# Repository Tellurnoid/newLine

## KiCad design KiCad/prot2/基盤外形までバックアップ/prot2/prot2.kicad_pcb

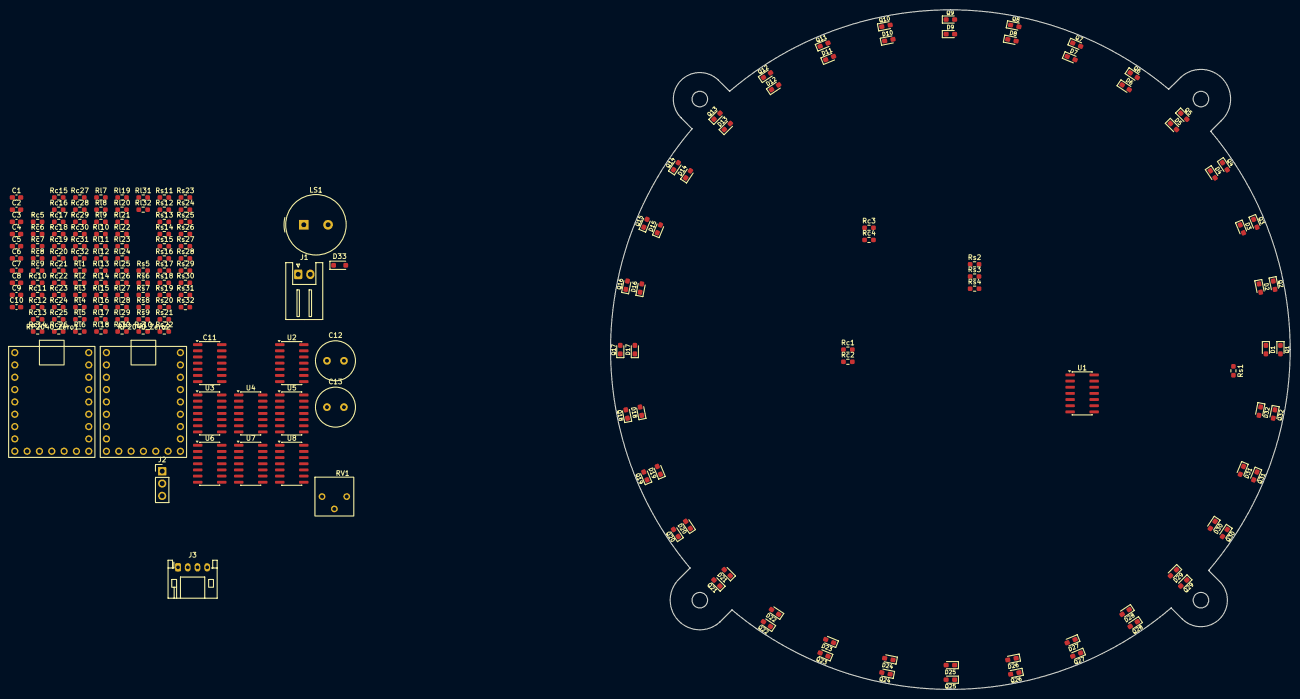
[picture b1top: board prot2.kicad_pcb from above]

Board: 2 copper layers, 140.0 x 140.0 mm, 193 parts (0 on the bottom side), 74 nets, no tracks yet.

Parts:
C1, C2, C3, C4, C5, C6, C7, C8, C9, C10: C; C_0603_1608Metric_Pad1.08x0.95mm_HandSolder
C11: C_Polarized_Small_US; SOIC-14_3.9x8.7mm_P1.27mm
C12, C13: C_Polarized_Small_US; C_Radial_D8.0mm_H11.5mm_P3.50mm
D1, D2, D3, D4, D5, D6, D7, D8, D9, D10, D11, D12, D13, D14, D15, D16, D17, D18, D19, D20, D21, D22, D23, D24, D25, D26, D27, D28, D29, D30, D31, D32: LED; LED_0603_1608Metric_Pad1.05x0.95mm_HandSolder
D33: D_Schottky; D_SOD-323_HandSoldering
H1, H2, H3, H4: MountingHole; MountingHole_3.2mm_M3
J1: Conn_01x02_Socket; JST_XH_S2B-XH-A_1x02_P2.50mm_Horizontal
J2: LED_SW; PinHeader_1x03_P2.54mm_Vertical
J3: Conn_01x04_Socket; JST_PH_S4B-PH-K_1x04_P2.00mm_Horizontal
LS1: Speaker_Crystal; Buzzer_TDK_PS1240P02BT_D12.2mm_H6.5mm
Q1, Q2, Q3, Q4, Q5, Q6, Q7, Q8, Q9, Q10, Q11, Q12, Q13, Q14, Q15, Q16, Q17, Q18, Q19, Q20, Q21, Q22, Q23, Q24, Q25, Q26, Q27, Q28, Q29, Q30, Q31, Q32: Q_Photo_NPN; LED_0603_1608Metric_Pad1.05x0.95mm_HandSolder
RP2040_Zero1, RP2040_Zero2: RP2040_zero
RV1: R_Potentiometer_Trim; hankotei_node
Rc1, Rc2, Rc3, Rc4, Rc5, Rc6, Rc7, Rc8, Rc9, Rc10, Rc11, Rc12, Rc13, Rc14, Rc15, Rc16, Rc17, Rc18, Rc19, Rc20, Rc21, Rc22, Rc23, Rc24, Rc25, Rc26, Rc27, Rc28, Rc29, Rc30, Rc31, Rc32: R; R_0603_1608Metric_Pad0.98x0.95mm_HandSolder
Rl1, Rl2, Rl3, Rl4, Rl5, Rl6, Rl7, Rl8, Rl9, Rl10, Rl11, Rl12, Rl13, Rl14, Rl15, Rl16, Rl17, Rl18, Rl19, Rl20, Rl21, Rl22, Rl23, Rl24, Rl25, Rl26, Rl27, Rl28, Rl29, Rl30, Rl31, Rl32: R; R_0603_1608Metric_Pad0.98x0.95mm_HandSolder
Rs1, Rs2, Rs3, Rs4, Rs5, Rs6, Rs7, Rs8, Rs9, Rs10, Rs11, Rs12, Rs13, Rs14, Rs15, Rs16, Rs17, Rs18, Rs19, Rs20, Rs21, Rs22, Rs23, Rs24, Rs25, Rs26, Rs27, Rs28, Rs29, Rs30, Rs31, Rs32: R; R_0603_1608Metric_Pad0.98x0.95mm_HandSolder
U1, U2, U3, U4, U5, U6, U7, U8: LM339; SOIC-14_3.9x8.7mm_P1.27mm

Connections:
1: Rc1.2, U1.2
2: Rc2.2, U1.1
3: Rc3.2, U1.13
4: Rc4.2, U1.14
5: Rc5.2, U2.2
6: Rc6.2, U2.1
7: Rc7.2, U2.13
8: Rc8.2, U2.14
9: Rc9.2, U3.2
10: Rc10.2, U3.1
11: Rc11.2, U3.13
12: Rc12.2, U3.14
13: Rc13.2, U4.2
14: Rc14.2, U4.1
15: Rc15.2, U4.13
16: Rc16.2, U4.14
17: Rc17.2, U5.2
18: Rc18.2, U5.1
19: Rc19.2, U5.13
20: Rc20.2, U5.14
21: Rc21.2, U6.2
22: Rc22.2, U6.1
23: Rc23.2, U6.13
24: Rc24.2, U6.14
25: Rc25.2, U7.2
26: Rc26.2, U7.1
27: Rc27.2, U7.13
28: Rc28.2, U7.14
29: Rc29.2, U8.2
30: Rc30.2, U8.1
31: Rc31.2, U8.13
32: Rc32.2, U8.14
GND: C1.2, C2.2, C3.2, C4.2, C5.2, C6.2, C7.2, C8.2, C9.2, C10.2, C11.2, C12.2, C13.2, J1.2, J3.4, RP2040_Zero1.22 (GND), RP2040_Zero2.22 (GND), RV1.3, Rl1.2, Rl2.2, Rl3.2, Rl4.2, Rl5.2, Rl6.2, Rl7.2, Rl8.2, Rl9.2, Rl10.2, Rl11.2, Rl12.2, Rl13.2, Rl14.2, Rl15.2, Rl16.2, Rl17.2, Rl18.2, Rl19.2, Rl20.2, Rl21.2, Rl22.2, Rl23.2, Rl24.2, Rl25.2, Rl26.2, Rl27.2, Rl28.2, Rl29.2, Rl30.2, Rl31.2, Rl32.2, Rs1.2, Rs2.2, Rs3.2, Rs4.2, Rs5.2, Rs6.2, Rs7.2, Rs8.2, Rs9.2, Rs10.2, Rs11.2, Rs12.2, Rs13.2, Rs14.2, Rs15.2, Rs16.2, Rs17.2, Rs18.2, Rs19.2, Rs20.2, Rs21.2, Rs22.2, Rs23.2, Rs24.2, Rs25.2, Rs26.2, Rs27.2, Rs28.2, Rs29.2, Rs30.2, Rs31.2, Rs32.2, U1.12 (V-), U2.12 (V-), U3.12 (V-), U4.12 (V-), U5.12 (V-), U6.12 (V-), U7.12 (V-), U8.12 (V-)
IMU_5V: C9.1, C10.1, C11.1, C12.1, D33.1 (K), RP2040_Zero1.23 (5V), RP2040_Zero2.23 (5V)
LED_5V: C13.1, D1.2 (A), D2.2 (A), D3.2 (A), D4.2 (A), D5.2 (A), D6.2 (A), D7.2 (A), D8.2 (A), D9.2 (A), D10.2 (A), D11.2 (A), D12.2 (A), D13.2 (A), D14.2 (A), D15.2 (A), D16.2 (A), D17.2 (A), D18.2 (A), D19.2 (A), D20.2 (A), D21.2 (A), D22.2 (A), D23.2 (A), D24.2 (A), D25.2 (A), D26.2 (A), D27.2 (A), D28.2 (A), D29.2 (A), D30.2 (A), D31.2 (A), D32.2 (A), J1.1, J2.3
unnamed: D1.1 (K), D2.1 (K), D3.1 (K), D4.1 (K), D5.1 (K), D6.1 (K), D7.1 (K), D8.1 (K), D9.1 (K), D10.1 (K), D11.1 (K), D12.1 (K), D13.1 (K), D14.1 (K), D15.1 (K), D16.1 (K), D17.1 (K), D18.1 (K), D19.1 (K), D20.1 (K), D21.1 (K), D22.1 (K), D23.1 (K), D24.1 (K), D25.1 (K), D26.1 (K), D27.1 (K), D28.1 (K), D29.1 (K), D30.1 (K), D31.1 (K), D32.1 (K), Rl1.1
unnamed: D33.2 (A), J3.3
unnamed: J2.1, J2.2
unnamed: Q1.2 (E), Q2.2 (E), Q3.2 (E), Q4.2 (E), Q5.2 (E), Q6.2 (E), Q7.2 (E), Q8.2 (E), Q9.2 (E), Q10.2 (E), Q11.2 (E), Q12.2 (E), Q13.2 (E), Q14.2 (E), Q15.2 (E), Q16.2 (E), Q17.2 (E), Q18.2 (E), Q19.2 (E), Q20.2 (E), Q21.2 (E), Q22.2 (E), Q23.2 (E), Q24.2 (E), Q25.2 (E), Q26.2 (E), Q27.2 (E), Q28.2 (E), Q29.2 (E), Q30.2 (E), Q31.2 (E), Q32.2 (E), Rs1.1, U1.4 (-)
unnamed: Rs2.1, U1.6 (-)
unnamed: Rs3.1, U1.10 (-)
unnamed: Rs4.1, U1.8 (-)
unnamed: Rs5.1, U2.4 (-)
unnamed: Rs6.1, U2.6 (-)
unnamed: Rs7.1, U2.10 (-)
unnamed: Rs8.1, U2.8 (-)
unnamed: Rs9.1, U3.4 (-)
unnamed: Rs10.1, U3.6 (-)
unnamed: Rs11.1, U3.10 (-)
unnamed: Rs12.1, U3.8 (-)
unnamed: Rs13.1, U4.4 (-)
unnamed: Rs14.1, U4.6 (-)
unnamed: Rs15.1, U4.10 (-)
unnamed: Rs16.1, U4.8 (-)
unnamed: Rs17.1, U5.4 (-)
unnamed: Rs18.1, U6.4 (-)
unnamed: Rs19.1, U7.4 (-)
unnamed: Rs20.1, U8.4 (-)
unnamed: Rs21.1, U5.6 (-)
unnamed: Rs22.1, U6.6 (-)
unnamed: Rs23.1, U7.6 (-)
unnamed: Rs24.1, U8.6 (-)
unnamed: Rs25.1, U5.10 (-)
unnamed: Rs26.1, U6.10 (-)
unnamed: Rs27.1, U7.10 (-)
unnamed: Rs28.1, U8.10 (-)
unnamed: Rs29.1, U5.8 (-)
unnamed: Rs30.1, U6.8 (-)
unnamed: Rs31.1, U7.8 (-)
unnamed: Rs32.1, U8.8 (-)
OUT_RX: J3.2, RP2040_Zero1.2 (1)
OUT_TX: J3.1, RP2040_Zero1.1 (0)
VCC: C1.1, C2.1, C3.1, C4.1, C5.1, C6.1, C7.1, C8.1, Q1.1 (C), Q2.1 (C), Q3.1 (C), Q4.1 (C), Q5.1 (C), Q6.1 (C), Q7.1 (C), Q8.1 (C), Q9.1 (C), Q10.1 (C), Q11.1 (C), Q12.1 (C), Q13.1 (C), Q14.1 (C), Q15.1 (C), Q16.1 (C), Q17.1 (C), Q18.1 (C), Q19.1 (C), Q20.1 (C), Q21.1 (C), Q22.1 (C), Q23.1 (C), Q24.1 (C), Q25.1 (C), Q26.1 (C), Q27.1 (C), Q28.1 (C), Q29.1 (C), Q30.1 (C), Q31.1 (C), Q32.1 (C), RP2040_Zero1.21 (3V3), RP2040_Zero2.21 (3V3), RV1.1, Rc1.1, Rc2.1, Rc3.1, Rc4.1, Rc5.1, Rc6.1, Rc7.1, Rc8.1, Rc9.1, Rc10.1, Rc11.1, Rc12.1, Rc13.1, Rc14.1, Rc15.1, Rc16.1, Rc17.1, Rc18.1, Rc19.1, Rc20.1, Rc21.1, Rc22.1, Rc23.1, Rc24.1, Rc25.1, Rc26.1, Rc27.1, Rc28.1, Rc29.1, Rc30.1, Rc31.1, Rc32.1, U1.3 (V+), U2.3 (V+), U3.3 (V+), U4.3 (V+), U5.3 (V+), U6.3 (V+), U7.3 (V+), U8.3 (V+)
conp_+: RV1.2, U1.5 (+), U1.7 (+), U1.9 (+), U1.11 (+), U2.5 (+), U2.7 (+), U2.9 (+), U2.11 (+), U3.5 (+), U3.7 (+), U3.9 (+), U3.11 (+), U4.5 (+), U4.7 (+), U4.9 (+), U4.11 (+), U5.5 (+), U5.7 (+), U5.9 (+), U5.11 (+), U6.5 (+), U6.7 (+), U6.9 (+), U6.11 (+), U7.5 (+), U7.7 (+), U7.9 (+), U7.11 (+), U8.5 (+), U8.7 (+), U8.9 (+), U8.11 (+)

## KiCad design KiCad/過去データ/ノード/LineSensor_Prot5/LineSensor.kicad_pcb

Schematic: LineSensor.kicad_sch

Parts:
A1: Arduino_Nano_v2.x; Arduino_Nano
C2: C; CP_Radial_D5.0mm_P2.50mm
C3: C; C_Disc_D7.5mm_W2.5mm_P5.00mm
C4, C5, C6, C7, C8, C9, C10, C11: C; C_0603_1608Metric
CN1, CN2: C_Network04
D34, D35, D36, D37, D38, D39, D40, D41, D42, D43, D44, D45, D46, D47, D48, D49: LED; LED_0603_1608Metric
H1, H2, H3, H4: MountingHole; MountingHole_3.2mm_M3
J1: Conn_01x04_Socket; JST_XH_B4B-XH-A_1x04_P2.50mm_Vertical
J2: Conn_01x02_Socket; JST_XH_B2B-XH-A_1x02_P2.50mm_Vertical
Q1, Q2, Q3, Q4, Q5, Q6, Q7, Q8, Q9, Q10, Q11, Q12, Q13, Q14, Q15, Q16: Q_Photo_NPN; NJL7502R
Q17: NMOS; TO-251-3-1EP_Horizontal_TabDown
R1, R2, R3, R4, R5, R6, R7, R8, R9, R10, R11, R12, R13, R14, R15, R16, R17, R18, R19, R20, R21, R22, R23, R24, R25, R26, R27, R28, R29, R30, R31, R32, R33, R34, R35, R36, R37, R38, R39, R40, R41, R42, R43, R44, R45, R46, R55, R56: R; R_0603_1608Metric_Pad0.98x0.95mm_HandSolder
R49, R50, R51, R84, R85: R; R_Axial_DIN0207_L6.3mm_D2.5mm_P7.62mm_Horizontal
RV1: R_Potentiometer_Trim; 名称未設定
SW2: SW_DPST_x2; PinSocket_1x03_P2.54mm_Vertical
U2, U3, U4, U5, U6, U7, U8, U9: LM393; SOIC-8_3.9x4.9mm_P1.27mm

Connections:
GND: A1.4 (GND), A1.29 (GND), C2.1, C3.2, C4.2, C5.2, C6.2, C7.2, C8.2, C9.2, C10.2, C11.2, J1.3, J2.2, Q17.3 (S), R1.2, R2.2, R3.2, R4.2, R9.2, R10.2, R11.2, R12.2, R13.2, R14.2, R15.2, R16.2, R17.2, R18.2, R19.2, R20.2, R50.2, R85.1, RV1.3, U2.4 (V-), U3.4 (V-), U4.4 (V-), U5.4 (V-), U6.4 (V-), U7.4 (V-), U8.4 (V-), U9.4 (V-)
unnamed: A1.2 (D0/RX), J1.2
unnamed: A1.1 (D1/TX), R49.2
unnamed: A1.13 (D10), R84.1
unnamed: D34.1 (K), R55.1
unnamed: D35.1 (K), R56.1
unnamed: D36.1 (K), R40.1
unnamed: D37.1 (K), R41.1
unnamed: D38.1 (K), R42.1
unnamed: D39.1 (K), R43.1
unnamed: D40.1 (K), R44.1
unnamed: D41.1 (K), R45.1
unnamed: D42.1 (K), R46.1
unnamed: D43.1 (K), R39.1
unnamed: D44.1 (K), R38.1
unnamed: D45.1 (K), R37.1
unnamed: D46.1 (K), R36.1
unnamed: D47.1 (K), R35.1
unnamed: D48.1 (K), R34.1
unnamed: D49.1 (K), R33.1
unnamed: J1.1, R49.1, R51.1
unnamed: J2.1, SW2.2 (B)
unnamed: Q1.2 (E), R4.1, U3.2 (-)
unnamed: Q2.2 (E), R3.1, U3.6 (-)
unnamed: Q3.2 (E), R2.1, U4.2 (-)
unnamed: Q4.2 (E), R1.1, U4.6 (-)
unnamed: Q5.2 (E), R13.1, U7.2 (-)
unnamed: Q6.2 (E), R14.1, U7.6 (-)
unnamed: Q7.2 (E), R16.1, U8.6 (-)
unnamed: Q8.2 (E), R15.1, U8.2 (-)
unnamed: Q9.2 (E), R9.1, U6.6 (-)
unnamed: Q10.2 (E), R10.1, U6.2 (-)
unnamed: Q11.2 (E), R11.1, U5.6 (-)
unnamed: Q12.2 (E), R12.1, U5.2 (-)
unnamed: Q13.2 (E), R17.1, U9.3 (+)
unnamed: Q14.2 (E), R18.1, U9.5 (+)
unnamed: Q15.2 (E), R19.1, U2.2 (-)
unnamed: Q16.2 (E), R20.1, U2.6 (-)
unnamed: Q17.1 (D), R33.2, R34.2, R35.2, R36.2, R37.2, R38.2, R39.2, R40.2, R41.2, R42.2, R43.2, R44.2, R45.2, R46.2, R55.2, R56.2
unnamed: Q17.2 (G), R84.2, R85.2
unnamed: R50.1, R51.2
unnamed: RV1.2, U2.3 (+), U2.5 (+), U3.3 (+), U3.5 (+), U4.3 (+), U4.5 (+), U5.3 (+), U5.5 (+), U6.3 (+), U6.5 (+), U7.3 (+), U7.5 (+), U8.3 (+), U8.5 (+), U9.2 (-), U9.6 (-)
U2A: A1.9 (D6), R31.2, U2.1
U2B: A1.10 (D7), R32.2, U2.7
U3A: A1.14 (D11), R5.2, U4.7
U3B: A1.15 (D12), R6.2, U4.1
U4A: A1.20 (A1), R7.2, U3.7
U4B: A1.19 (A0), R8.2, U3.1
U5A: A1.22 (A3), R24.2, U5.1
U5B: A1.21 (A2), R23.2, U5.7
U6A: A1.23 (A4), R22.2, U6.1
U6B: A1.24 (A5), R21.2, U6.7
U7A: A1.7 (D4), R28.2, U7.1
U7B: A1.8 (D5), R27.2, U7.7
U8A: A1.5 (D2), R26.2, U8.1
U8B: A1.6 (D3), R25.2, U8.7
U9A: A1.12 (D9), R29.2, U9.1
U9B: A1.11 (D8), R30.2, U9.7
VCC: A1.27 (+5V), C2.2, C3.1, C4.1, C5.1, C6.1, C7.1, C8.1, C9.1, C10.1, C11.1, D34.2 (A), D35.2 (A), D36.2 (A), D37.2 (A), D38.2 (A), D39.2 (A), D40.2 (A), D41.2 (A), D42.2 (A), D43.2 (A), D44.2 (A), D45.2 (A), D46.2 (A), D47.2 (A), D48.2 (A), D49.2 (A), J1.4, Q1.1 (C), Q2.1 (C), Q3.1 (C), Q4.1 (C), Q5.1 (C), Q6.1 (C), Q7.1 (C), Q8.1 (C), Q9.1 (C), Q10.1 (C), Q11.1 (C), Q12.1 (C), Q13.1 (C), Q14.1 (C), Q15.1 (C), Q16.1 (C), R5.1, R6.1, R7.1, R8.1, R21.1, R22.1, R23.1, R24.1, R25.1, R26.1, R27.1, R28.1, R29.1, R30.1, R31.1, R32.1, RV1.1, SW2.1 (A), U2.8 (V+), U3.8 (V+), U4.8 (V+), U5.8 (V+), U6.8 (V+), U7.8 (V+), U8.8 (V+), U9.8 (V+)

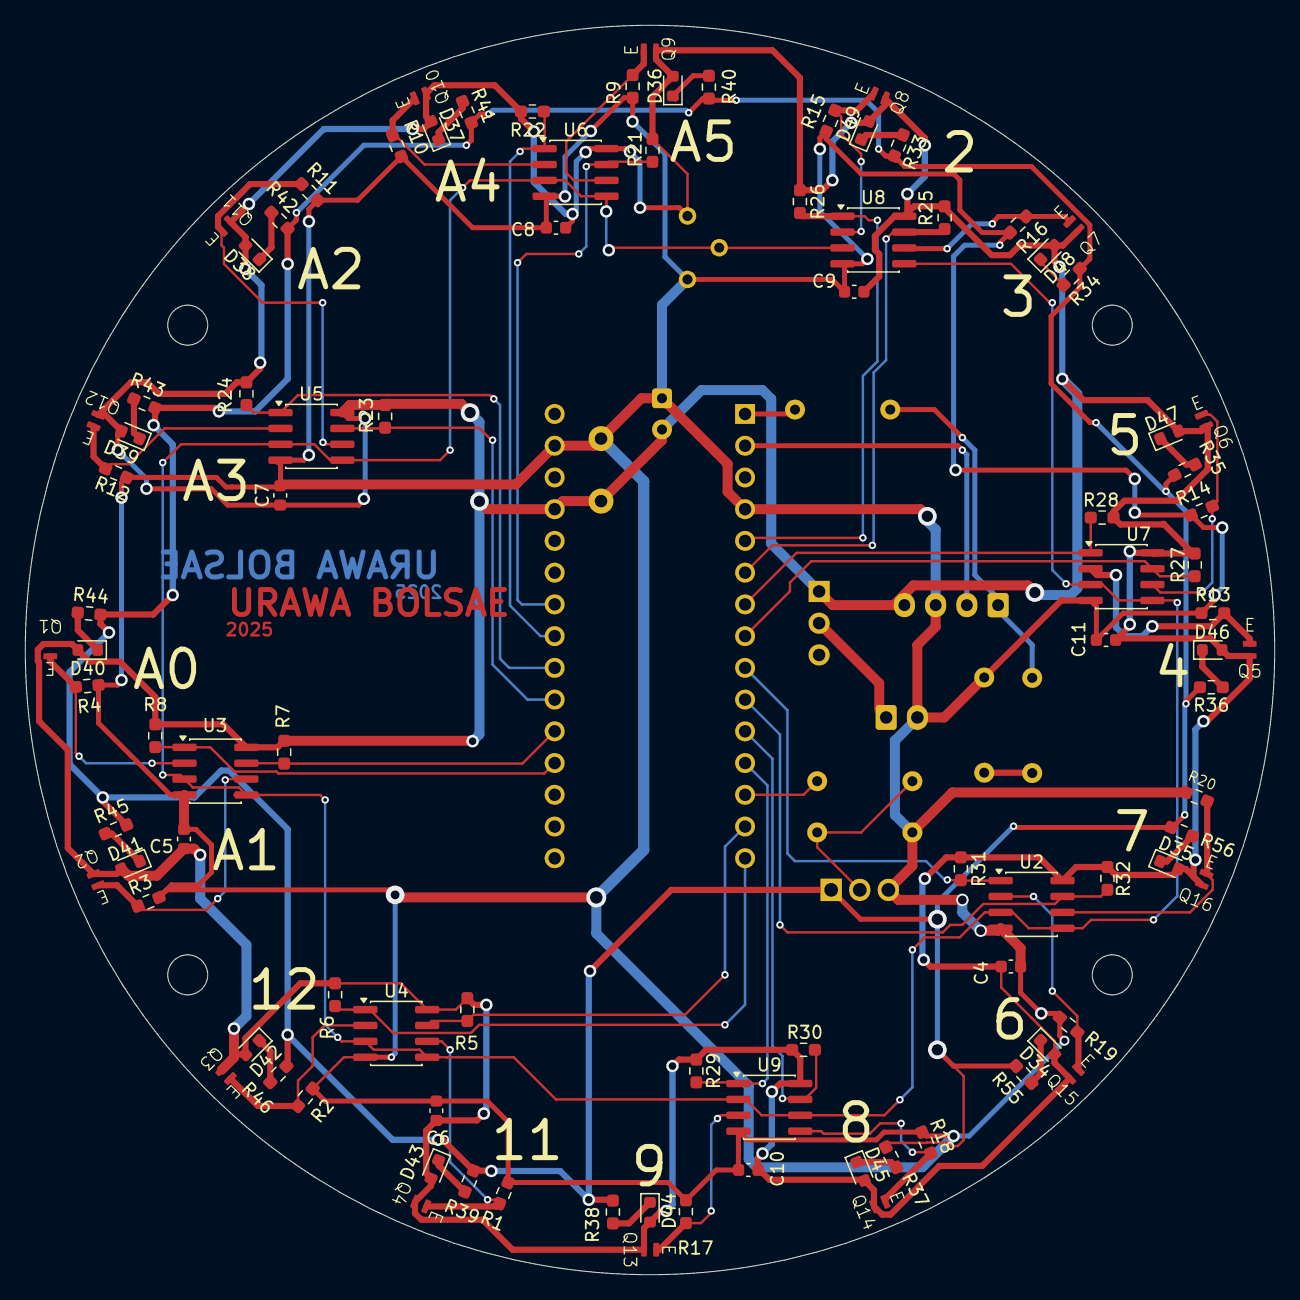
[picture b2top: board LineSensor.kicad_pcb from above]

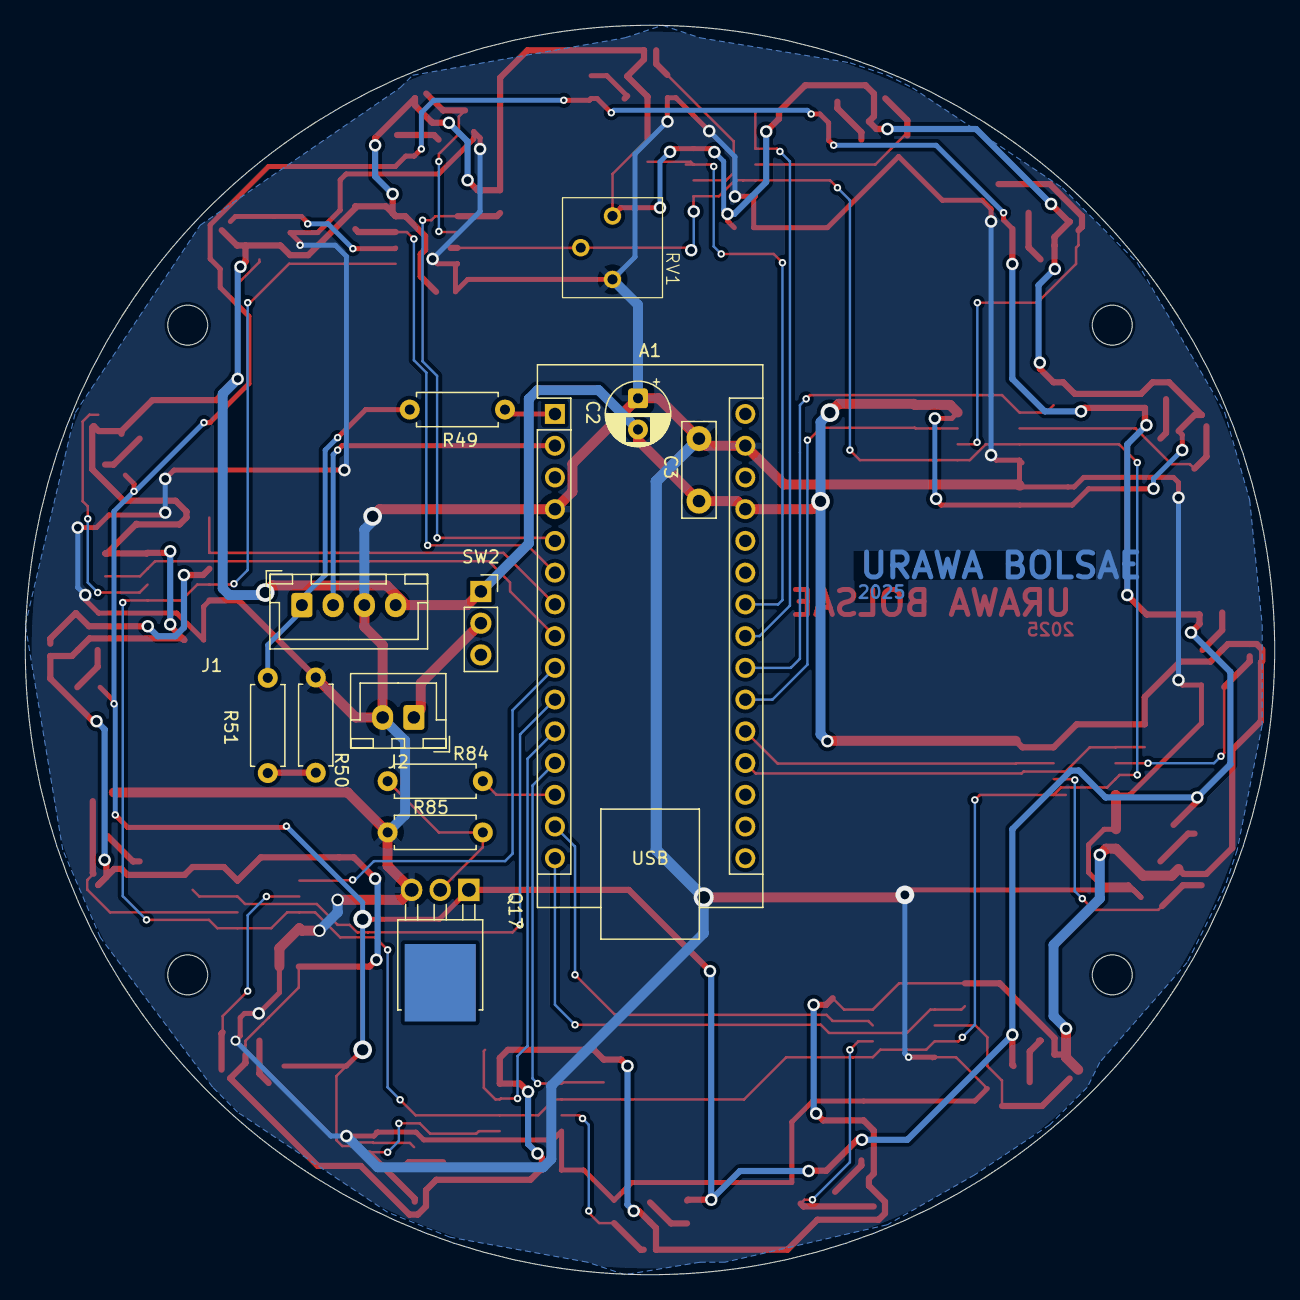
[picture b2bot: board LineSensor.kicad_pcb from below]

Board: 2 copper layers, 100.0 x 100.0 mm, 113 parts (13 on the bottom side), 59 nets.

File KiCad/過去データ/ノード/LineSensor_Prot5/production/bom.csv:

Designator,Footprint,Quantity,Value,LCSC Part #
A1,Arduino_Nano,1,Arduino_Nano_v2.x,
"C10, C11, C4, C5, C6, C7, C8, C9",0603,8,C,
C2,CP_Radial_D5.0mm_P2.50mm,1,C,
C3,C_Disc_D7.5mm_W2.5mm_P5.00mm,1,C,
"D34, D35, D36, D37, D38, D39, D40, D41, D42, D43, D44, D45, D46, D47, D48, D49",0603,16,LED,
J1,JST_XH_B4B-XH-A_1x04_P2.50mm_Vertical,1,Conn_01x04_Socket,
J2,JST_XH_B2B-XH-A_1x02_P2.50mm_Vertical,1,Conn_01x02_Socket,
"Q1, Q10, Q11, Q12, Q13, Q14, Q15, Q16, Q2, Q3, Q4, Q5, Q6, Q7, Q8, Q9",NJL7502R,16,Q_Photo_NPN,
Q17,TO-251-3-1EP_Horizontal_TabDown,1,NMOS,
"R1, R10, R11, R12, R13, R14, R15, R16, R17, R18, R19, R2, R20, R21, R22, R23, R24, R25, R26, R27, R28, R29, R3, R30, R31, R32, R33, R34, R35, R36, R37, R38, R39, R4, R40, R41, R42, R43, R44, R45, R46, R5, R55, R56, R6, R7, R8, R9",0603,48,R,
"R49, R50, R51, R84, R85",R_Axial_DIN0207_L6.3mm_D2.5mm_P7.62mm_Horizontal,5,R,
RV1,名称未設定,1,R_Potentiometer_Trim,
SW2,PinSocket_1x03_P2.54mm_Vertical,1,SW_DPST_x2,
"U2, U3, U4, U5, U6, U7, U8, U9",SOIC-8_3.9x4.9mm_P1.27mm,8,LM393,

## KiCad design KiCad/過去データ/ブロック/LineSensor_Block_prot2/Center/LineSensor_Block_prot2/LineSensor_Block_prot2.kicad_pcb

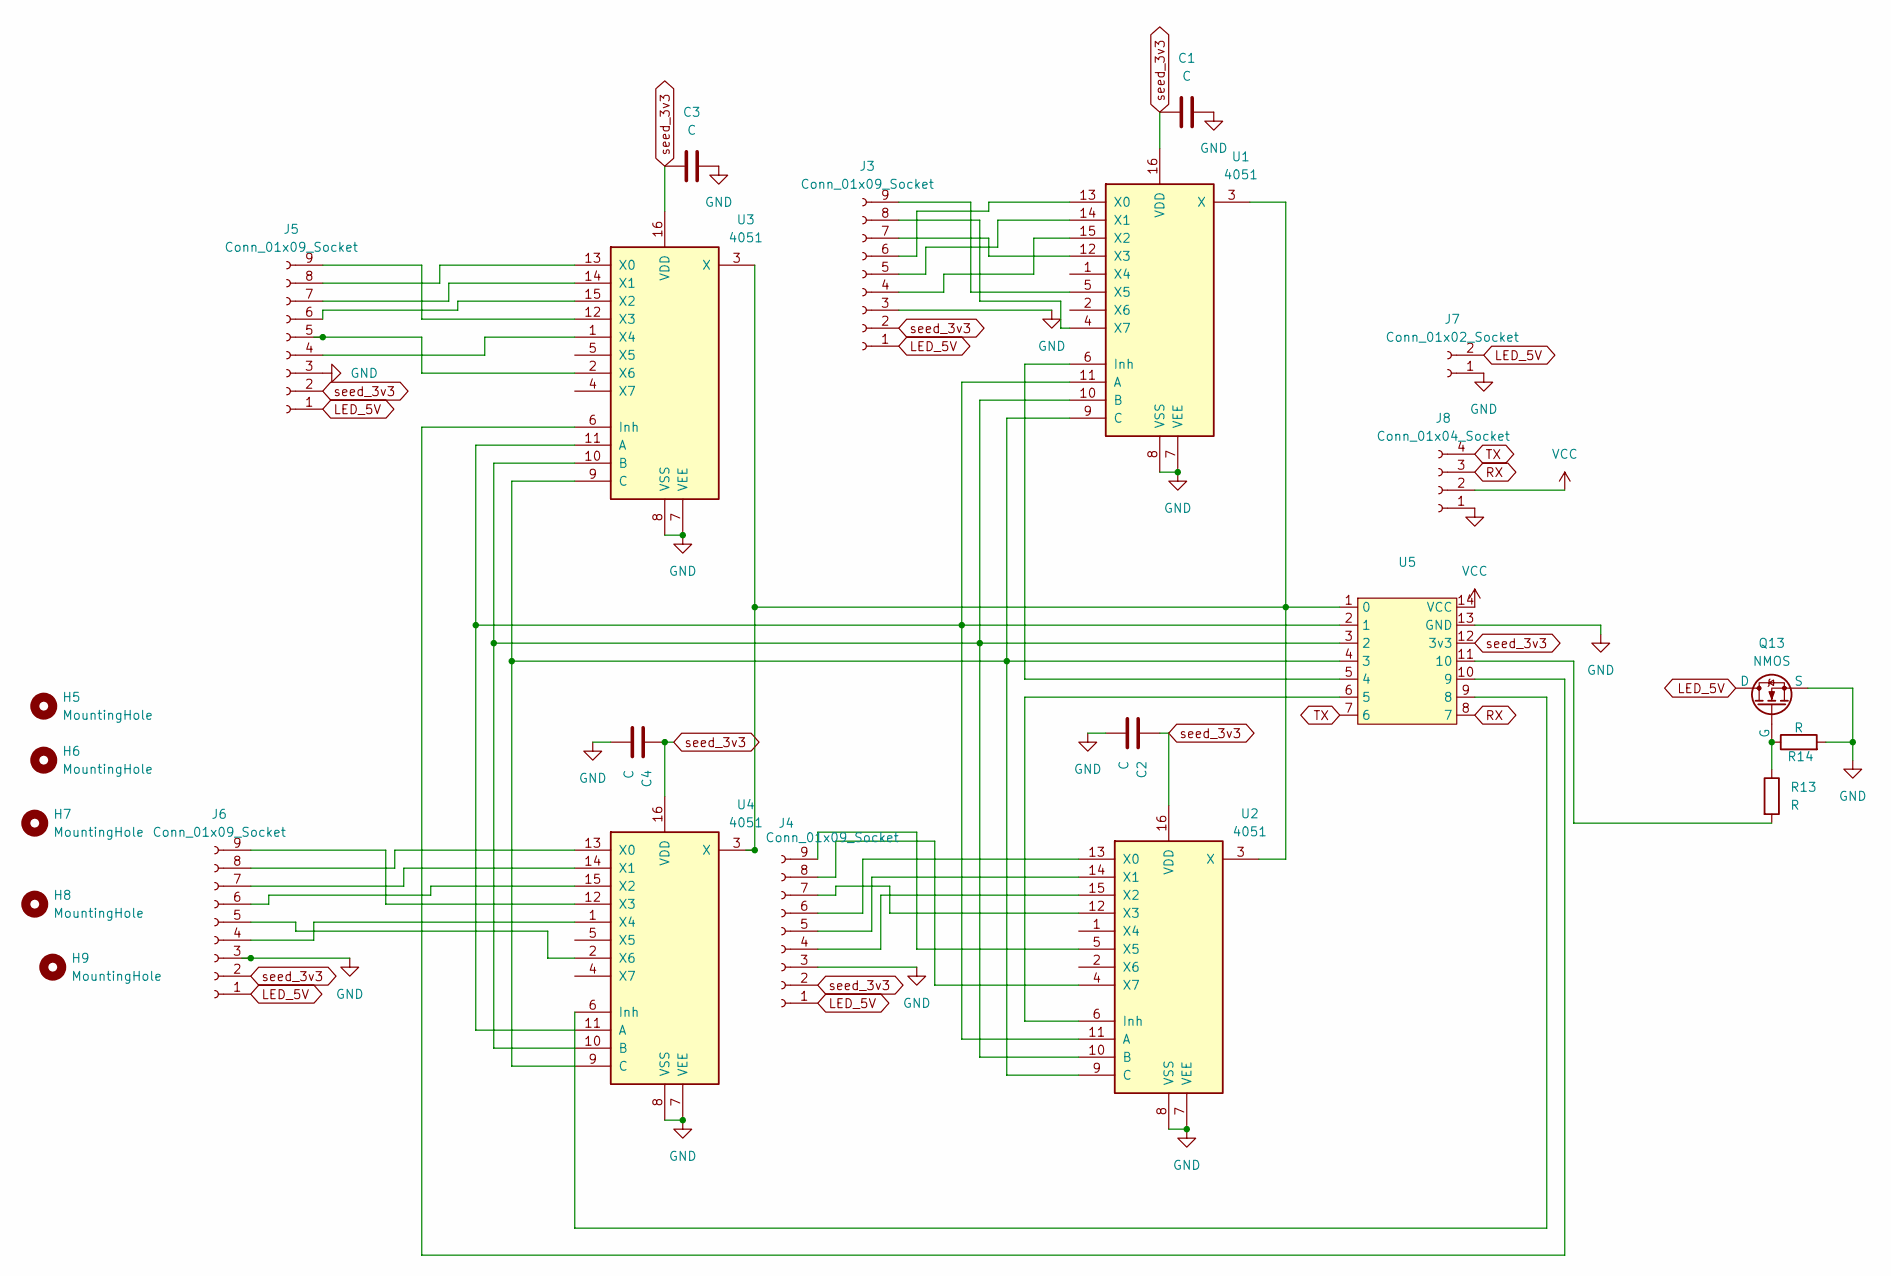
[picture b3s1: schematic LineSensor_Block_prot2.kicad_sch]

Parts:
C1, C2, C3, C4: C; C_0603_1608Metric
H5, H6, H7, H8, H9: MountingHole; MountingHole_3.2mm_M3
J3, J4, J5, J6: Conn_01x09_Socket; PinHeader_1x09_P2.54mm_Horizontal_EDITED
J7: Conn_01x02_Socket; JST_XH_S2B-XH-A-1_1x02_P2.50mm_Horizontal
J8: Conn_01x04_Socket; JST_XH_S4B-XH-A-1_1x04_P2.50mm_Horizontal
Q13: NMOS; TO-251-3-1EP_Horizontal_TabDown
R13, R14: R; R_Axial_DIN0207_L6.3mm_D2.5mm_P10.16mm_Horizontal
U1, U2, U3, U4: 4051; CERDIP-16_W7.62mm_SideBrazed_LongPads_pin_EDITED
U5: 名称未設定

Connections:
GND: C1.2, C2.2, C3.2, C4.2, J3.3, J4.3, J5.3, J6.3, J7.1, J8.1, Q13.3 (S), R14.2, U1.7 (VEE), U1.8 (VSS), U2.7 (VEE), U2.8 (VSS), U3.7 (VEE), U3.8 (VSS), U4.7 (VEE), U4.8 (VSS), U5.13 (GND)
LED_5V: J3.1, J4.1, J5.1, J6.1, J7.2, Q13.1 (D)
unnamed: J3.4, U1.15 (X2)
unnamed: J3.5, U1.14 (X1)
unnamed: J3.6, U1.13 (X0)
unnamed: J3.7, U1.12 (X3)
unnamed: J3.8, U1.4 (X7)
unnamed: J3.9, U1.5 (X5)
unnamed: J4.4, U2.15 (X2)
unnamed: J4.5, U2.14 (X1)
unnamed: J4.6, U2.13 (X0)
unnamed: J4.7, U2.12 (X3)
unnamed: J4.8, U2.4 (X7)
unnamed: J4.9, U2.5 (X5)
unnamed: J5.4, U3.1 (X4)
unnamed: J5.5, U3.2 (X6)
unnamed: J5.6, U3.15 (X2)
unnamed: J5.7, U3.14 (X1)
unnamed: J5.8, U3.13 (X0)
unnamed: J5.9, U3.12 (X3)
unnamed: J6.4, U4.1 (X4)
unnamed: J6.5, U4.2 (X6)
unnamed: J6.6, U4.15 (X2)
unnamed: J6.7, U4.14 (X1)
unnamed: J6.8, U4.13 (X0)
unnamed: J6.9, U4.12 (X3)
unnamed: Q13.2 (G), R13.1, R14.1
unnamed: U1.11 (A), U2.11 (A), U3.11 (A), U4.11 (A), U5.2 (1)
unnamed: U1.10 (B), U2.10 (B), U3.10 (B), U4.10 (B), U5.3 (2)
unnamed: U1.9 (C), U2.9 (C), U3.9 (C), U4.9 (C), U5.4 (3)
unnamed: U1.6 (Inh), U5.5 (4)
unnamed: U1.3 (X), U2.3 (X), U3.3 (X), U4.3 (X), U5.1 (0)
unnamed: U2.6 (Inh), U5.6 (5)
unnamed: U3.6 (Inh), U5.10 (9)
unnamed: U4.6 (Inh), U5.9 (8)
unnamed: R13.2, U5.11 (10)
RX: J8.3, U5.8 (7)
TX: J8.4, U5.7 (6)
VCC: J8.2, U5.14 (VCC)
seed_3v3: C1.1, C2.1, C3.1, C4.1, J3.2, J4.2, J5.2, J6.2, U1.16 (VDD), U2.16 (VDD), U3.16 (VDD), U4.16 (VDD), U5.12 (3v3)

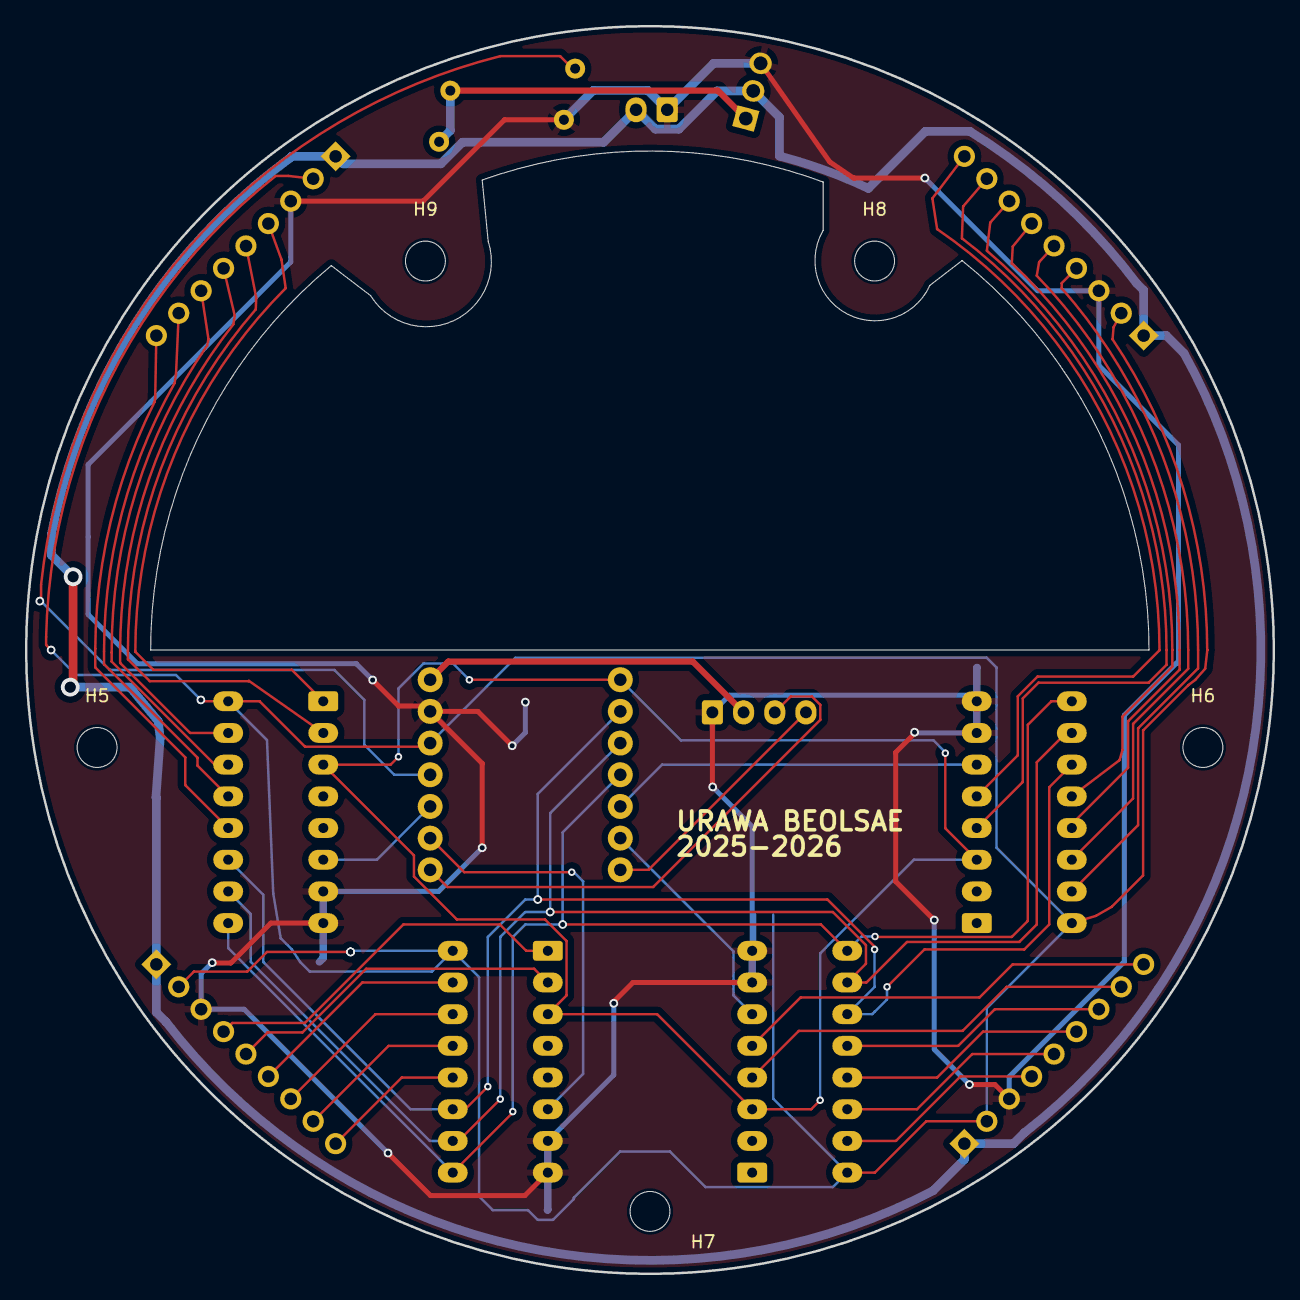
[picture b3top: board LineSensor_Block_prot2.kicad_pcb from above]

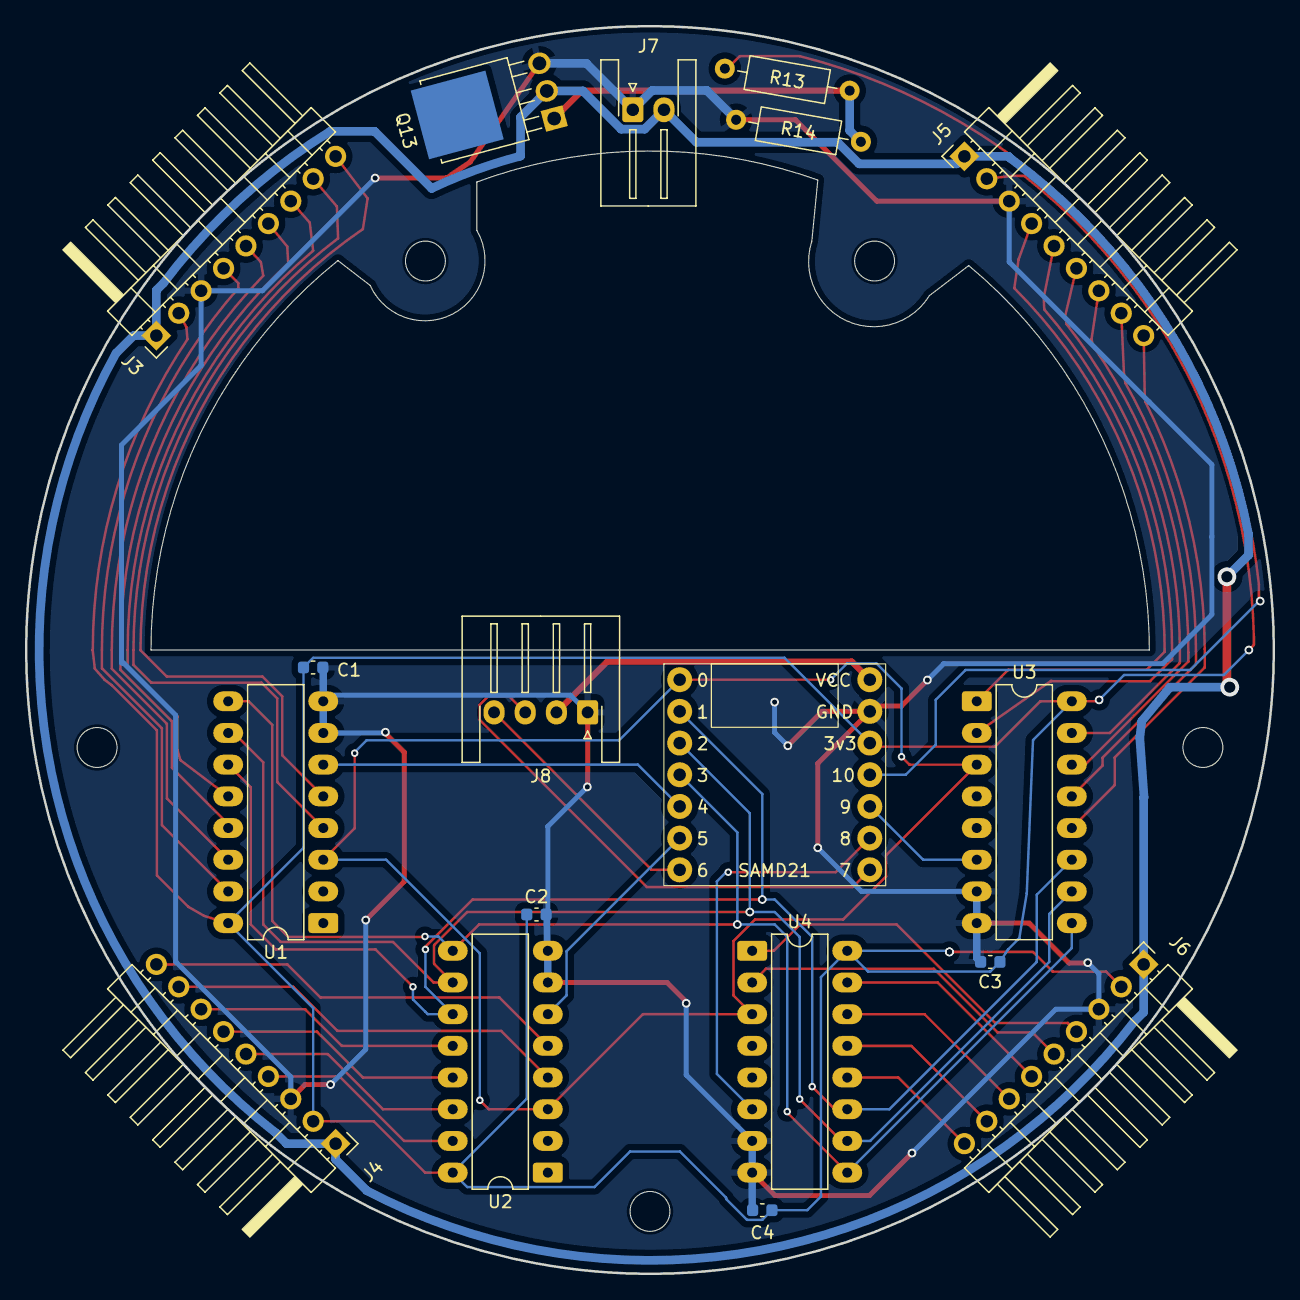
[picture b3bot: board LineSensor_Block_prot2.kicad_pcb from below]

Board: 2 copper layers, 100.0 x 100.0 mm, 23 parts (18 on the bottom side), 40 nets.

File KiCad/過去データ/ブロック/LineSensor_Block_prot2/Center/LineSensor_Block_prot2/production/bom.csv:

Designator,Footprint,Quantity,Value,LCSC Part #
"C1, C2, C3, C4",0603,4,C,
"J3, J4, J5, J6",PinHeader_1x09_P2.54mm_Horizontal_EDITED,4,Conn_01x09_Socket,
J7,JST_XH_S2B-XH-A-1_1x02_P2.50mm_Horizontal,1,Conn_01x02_Socket,
J8,JST_XH_S4B-XH-A-1_1x04_P2.50mm_Horizontal,1,Conn_01x04_Socket,
Q13,TO-251-3-1EP_Horizontal_TabDown,1,NMOS,
"R13, R14",R_Axial_DIN0207_L6.3mm_D2.5mm_P10.16mm_Horizontal,2,R,
"U1, U2, U3, U4",CERDIP-16_W7.62mm_SideBrazed_LongPads_pin_EDITED,4,4051,
U5,名称未設定,1,~,
